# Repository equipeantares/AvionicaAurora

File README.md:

# Icaro-I (Aviônica Aurora V1.0)

## Introdução 

### Motivação

A equipe Antares de espaçomodelismo da Unicamp tem como um de seus projetos desenvolvidos o foguete Aurora. Trata-se de um foguete de propulsão sólida com apogeu esperado de 1km. Como parte dos requisitos necessários para ter sucesso na missão, o foguete precisa de um sistema de aviônica que será responsável por coletar dados e tomar decisões previamente programadas durante o voo. 

### Objetivo

Sendo assim, o objetivo deste projeto é desenvolver um sistema de aviônica capaz de detectar o apogeu programado e acionar o sistema de recuperação. Deve também ser capaz de transmitir os dados de voo ao solo em tempo real e coletar informações sobre a posição do foguete, possibilitando sua localização após aterrisagem. Além disso, deve ser dimensionada para caber na estrutura interna do foguete.

### Soluções comerciais

Pelo fato de o sistema precisar ser personalizado, se ajustando ao sistema presente no foguete e aos demais requisitos específicos do projeto, não existem alternativas comerciais que cumpram integralmente o objetivo.

## Especificação
    - Microcontrolador: o dispositivo deverá ser capaz de fazer processamentos lógicos, sendo assim necessário um microcontrolador. Por motivos de acessibilidade e familiaridade, será utilizada a plataforma Arduino no MCU ESP-8266 12F.

    - Comunicação e dados: com o objetivo de enviar dados de telemetria do foguete, o dispositivo deverá ter um sistema transceptor, que será implementado por um módulo LoRA E32-915T20D. Além disso, contará com uma interface para cartão MicroSD, possibilitando que os dados brutos sejam armazenados para uma análise mais precisa posterior.

    - Interface: como interface, o dispositivo contará com conectores para alimentação externa, além de pinos seletores, que selecionam, principalmente, se o sistema é o principal ou uma redundância e se o acionamento será interno ou externo (para testes).

    - Ignição: a aviônica precisa implementar um sistema de ignição que será o responsável pela liberação da recuperação.

    - Alimentação: o sistema tem interface de alimentação externa.

    - Redundância: o dispositivo implementa solução para um sistema com redundância nos subsistemas críticos, provendo maior segurança.

    - Localização: a fim de garantir que seja possível localizar o foguete após o pouso, o sistema deve ser capaz de transmitir a posição em tempo real por meio de um sistema GPS e de emitir um aviso sonoro por meio de um buzzer.

    - Detecção de apogeu: para ser capaz de detectar o momento do apogeu, a aviônica deve implementar um altímetro.

## Pinagem

### Pinout conector Screw bateria 18650

Pino | Sinal
-----|------
1  | VBat
2  | GND

### Pinout conector Screw do Acionamento

Pino | Sinal
-----|------
  1  | NiCr_ISO
  2  | GND_ISO

### Pinout conector Screw da Redundancia

Pino | Sinal
-----|------
  1  | Redundancy_IN
  2  | Redundancy_OUT

### Pinout conector Seleção Redundância

Pino | Sinal
-----|------
  1  | Redundancy_OUT
  2  | IGN
  3  | Main_IGN

### Pinout conector Transistor PNP acionamento (interno)

Pino | Sinal
-----|------
  1  | Emissor
  2  | Coletor

### Pinout conector Optoacoplador acionamento (externo)

Pino | Sinal
-----|------
  1  | Coletor
  2  | Emissor

## Testes

    A fim de garantir que o sistema seja seguro e que tudo funcione como esperado, é necessário realizar testes controlados de cada parte do sistema, tentando antecipar possíveis falhas que possam ocorrer. 
    Como o sistema de ignição não pode ter acionamento indesejado, devem ocorrer testes em ambientes adversos, como, por exemplo, com componentes desconectados, e o resultado esperado é que o sistema não ative em nenhuma dessas situações.
    Além disso, todos os sensores presentes devem ser validados.

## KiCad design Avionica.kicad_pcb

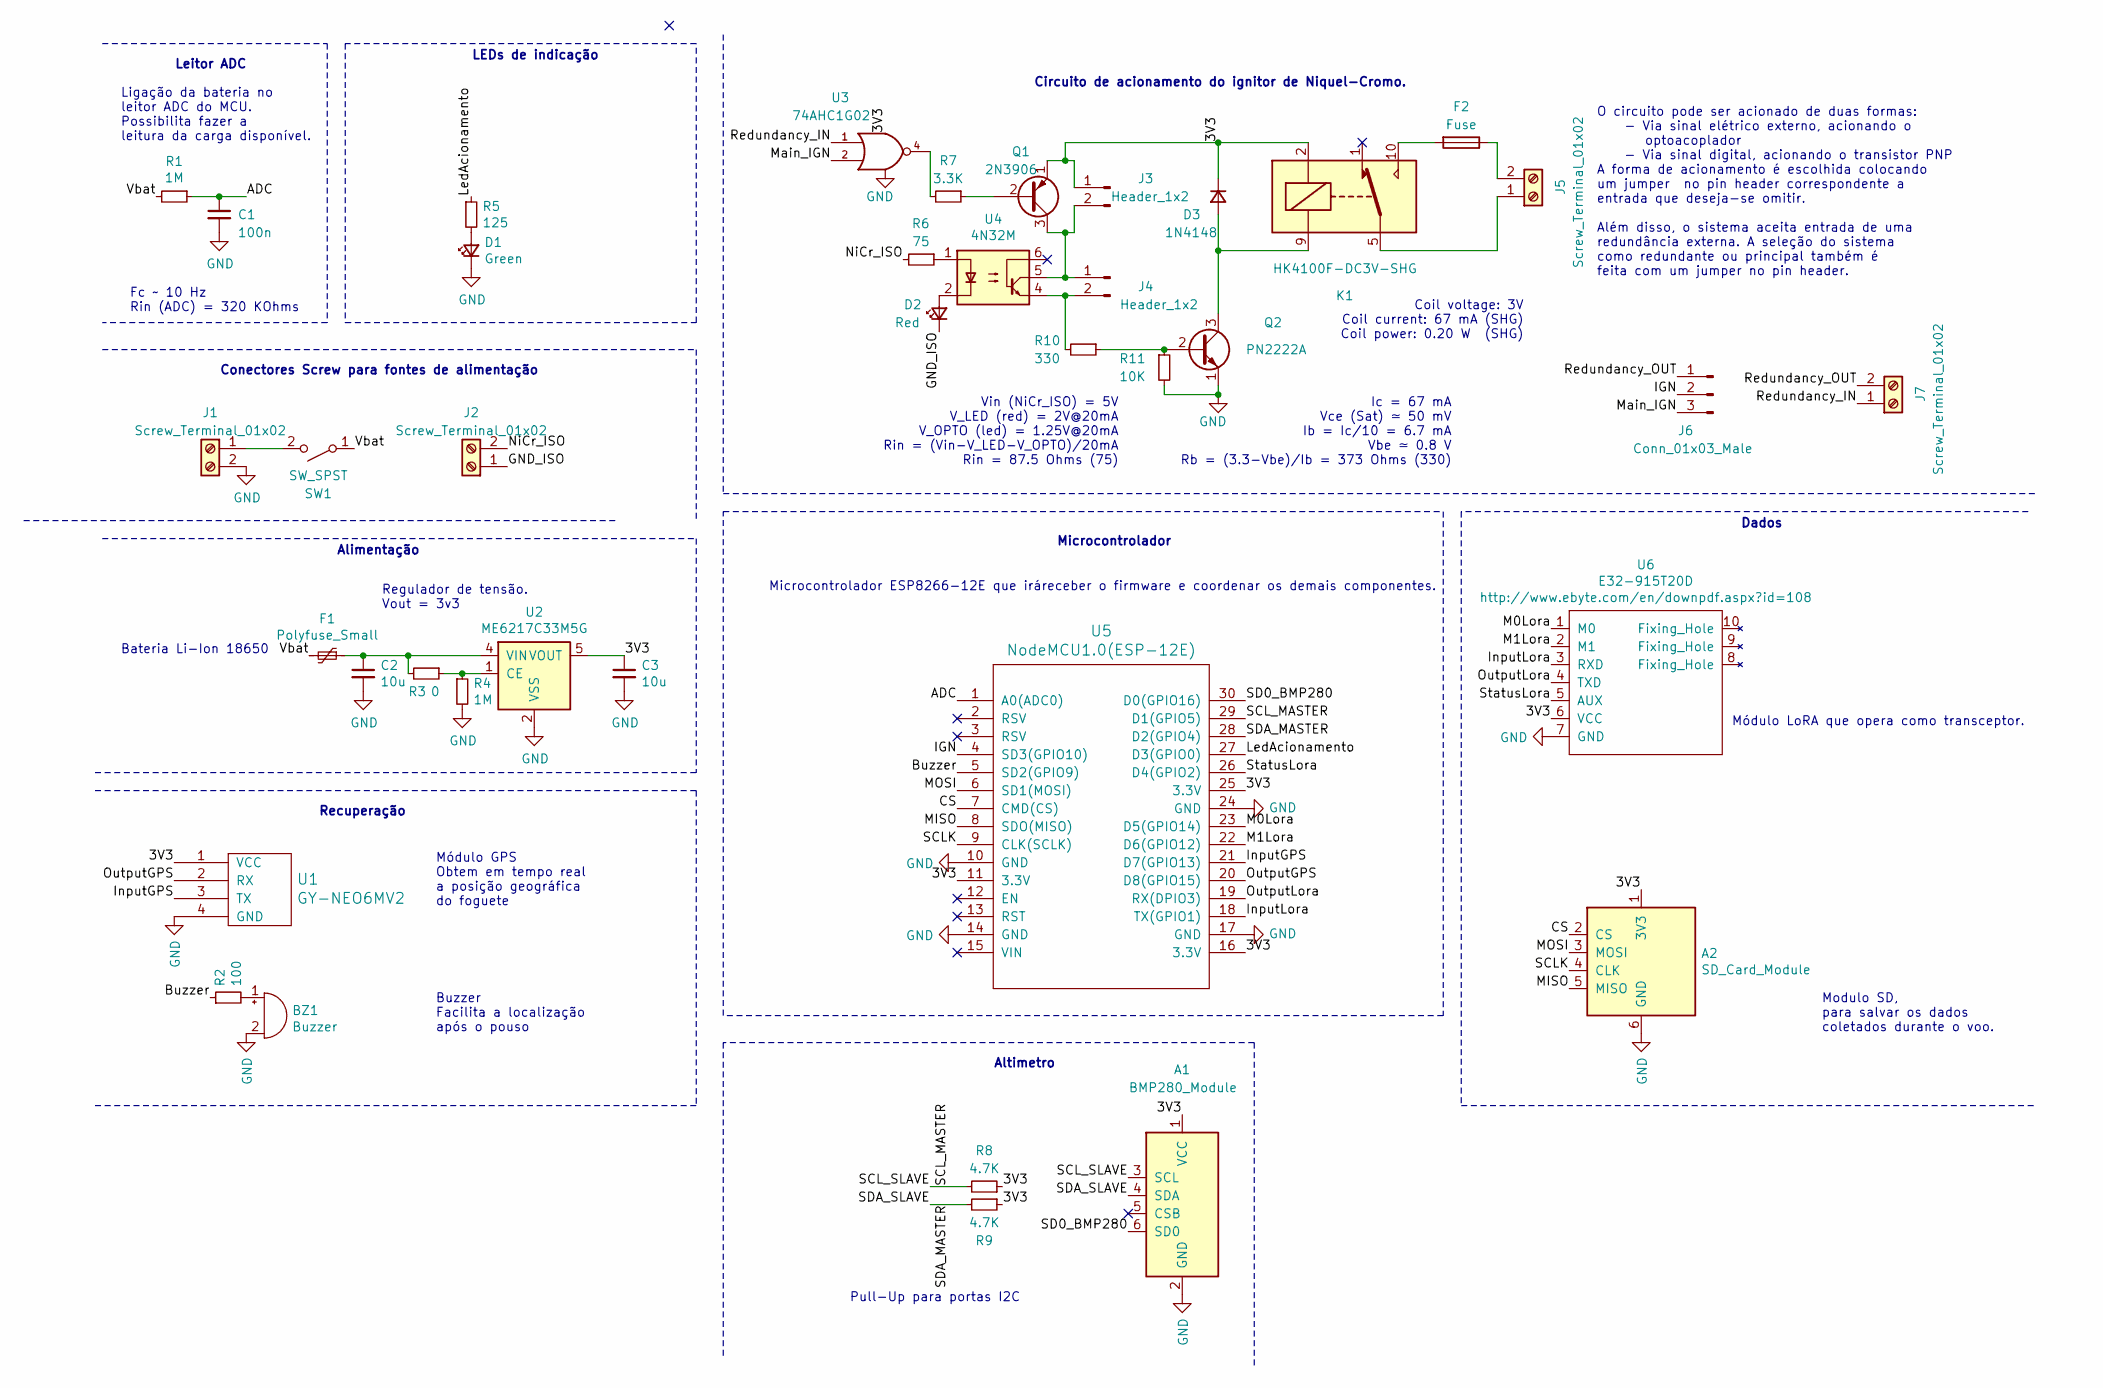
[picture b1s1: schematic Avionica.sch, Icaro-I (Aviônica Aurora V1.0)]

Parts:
A1: BMP280_Module
A2: SD_Card_Module
BZ1: Buzzer; Buzzer_12x9.5RM7.6
C1: 100n; C_0805_2012Metric
C2, C3: 10u; C_0805_2012Metric
D1: Green; LED_D3.0mm
D2: Red; LED_D3.0mm
D3: 1N4148; D_SOD-123
F1: Polyfuse_Small; Fuse_1206_3216Metric_Castellated
F2: Fuse; Fuseholder_Cylinder-5x20mm_Stelvio-Kontek_PTF78_Horizontal_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
J1, J2, J5, J7: Screw_Terminal_01x02; TerminalBlock_Phoenix_MKDS-1,5-2_1x02_P5.00mm_Horizontal
J3, J4: Header_1x2; Molex_KK-254_AE-6410-02A_1x02_P2.54mm_Vertical
J6: Conn_01x03_Male; Molex_KK-254_AE-6410-03A_1x03_P2.54mm_Vertical
K1: HK4100F-DC3V-SHG; Relay_SPDT_Omron_G5V-1
Q1: 2N3906; TO-92_Inline
Q2: PN2222A; TO-92_Inline
R1, R4: 1M; R_0805_2012Metric
R2: 100; R_0805_2012Metric
R3: 0; R_0805_2012Metric
R5: 125; R_0805_2012Metric
R6: 75; R_0805_2012Metric
R7: 3.3K; R_0805_2012Metric
R8, R9: 4.7K; R_0805_2012Metric
R10: 330; R_0805_2012Metric
R11: 10K; R_0805_2012Metric
SW1: SW_SPST; Screw_Switch
U1: GY-NEO6MV2
U2: ME6217C33M5G; SOT-23-5
U3: 74AHC1G02; SOT-23-5
U4: 4N32M; DIP-6_W7.62mm
U5: NodeMCU1.0(ESP-12E); ESP12F-Devkit-V3
U6: E32-915T20D; E32-xxxT20D

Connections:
/ADC: C1.1, R1.1, U5.1 (A0(ADC0))
/Buzzer: R2.1, U5.5 (SD2(GPIO9))
/CS: A2.2 (CS), U5.7 (CMD(CS))
/GND_ISO: D2.1 (K), J2.1
/IGN: J6.2, U5.4 (SD3(GPIO10))
/InputGPS: U1.3 (TX), U5.21 (D7(GPIO13))
/InputLora: U5.18 (TX(GPIO1)), U6.3 (RXD)
/LedAcionamento: R5.1, U5.27 (D3(GPIO0))
/M0Lora: U5.23 (D5(GPIO14)), U6.1 (M0)
/M1Lora: U5.22 (D6(GPIO12)), U6.2 (M1)
/MISO: A2.5 (MISO), U5.8 (SDO(MISO))
/MOSI: A2.3 (MOSI), U5.6 (SD1(MOSI))
/Main_IGN: J6.3, U3.2
/NiCr_ISO: J2.2, R6.2
/OutputGPS: U1.2 (RX), U5.20 (D8(GPIO15))
/OutputLora: U5.19 (RX(DPIO3)), U6.4 (TXD)
/Redundancy_IN: J7.1, U3.1
/Redundancy_OUT: J6.1, J7.2
/SCLK: A2.4 (CLK), U5.9 (CLK(SCLK))
/SCL_MASTER: A1.3 (SCL), R8.2, U5.29 (D1(GPIO5))
/SD0_BMP280: A1.6 (SD0), U5.30 (D0(GPIO16))
/SDA_MASTER: A1.4 (SDA), R9.2, U5.28 (D2(GPIO4))
/StatusLora: U5.26 (D4(GPIO2)), U6.5 (AUX)
/Vbat: F1.2, R1.2, SW1.1 (A)
GND: A1.2 (GND), A2.6 (GND), BZ1.2 (+), C1.2, C2.2, C3.2, D1.1 (K), J1.2, Q2.1 (E), R4.2, R11.2, U1.4 (GND), U2.2 (VSS), U3.3 (GND), U5.10 (GND), U5.14 (GND), U5.17 (GND), U5.24 (GND), U6.7 (GND)
unnamed: BZ1.1 (-), R2.2
unnamed: C2.1, F1.1, R3.2, U2.4 (VIN)
unnamed: D1.2 (A), R5.2
unnamed: D2.2 (A), U4.2
unnamed: D3.2 (A), K1.9, Q2.3 (C)
unnamed: F2.1, J5.2
unnamed: F2.2, K1.10
unnamed: J1.1, SW1.2 (B)
unnamed: J3.2, J4.1, Q1.3 (C), U4.5
unnamed: J4.2, R10.2, U4.4
unnamed: J5.1, K1.5, K1.6
unnamed: Q1.2 (B), R7.1
unnamed: Q2.2 (B), R10.1, R11.1
unnamed: R3.1, R4.1, U2.1 (CE)
unnamed: R6.1, U4.1
unnamed: R7.2, U3.4
VCC: A1.1 (VCC), A2.1 (3V3), C3.1, D3.1 (K), J3.1, K1.2, Q1.1 (E), R8.1, R9.1, U1.1 (VCC), U2.5 (VOUT), U3.5 (VCC), U5.11 (3.3V), U5.16 (3.3V), U5.25 (3.3V), U6.6 (VCC)

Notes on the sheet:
Coil voltage: 3V Coil current: 67 mA (SHG) Coil power: 0.20 W (SHG)
Fc ~~ 10 Hz Rin (ADC) = 320 KOhms
Regulador de tensão. Vout = 3v3
Conectores Screw para fontes de alimentação
LEDs de indicação
Ligação da bateria no leitor ADC do MCU. Possibilita fazer a leitura da carga disponível.
Módulo LoRA que opera como transceptor.
Microcontrolador ESP8266-12E que iráreceber o firmware e coordenar os demais componentes.
O circuito pode ser acionado de duas formas: - Via sinal elétrico externo, acionando o optoacoplador - Via sinal digital, acionando o transistor PNP A forma de acionamento é escolhida colocando um jumper no pin header correspondente a entrada que deseja-se omitir. Além disso, o sistema aceita entra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
Microcontrolador
Dados
Bateria Li-Ion 18650
Alimentação
Leitor ADC
Circuito de acionamento do ignitor de Niquel-Cromo.
Ic = 67 mA Vce (Sat) ≃ 50 mV Ib = Ic/10 = 6.7 mA Vbe ≃ 0.8 V Rb = (3.3-Vbe)/Ib = 373 Ohms (330)
Vin (NiCr_ISO) = 5V V_LED (red) = 2V@20mA V_OPTO (led) = 1.25V@20mA Rin = (Vin-V_LED-V_OPTO)/20mA Rin = 87.5 Ohms (75)
Recuperação
Altimetro
Pull-Up para portas I2C
Modulo SD, para salvar os dados coletados durante o voo.
Módulo GPS Obtem em tempo real a posição geográfica do foguete
Buzzer Facilita a localização após o pouso

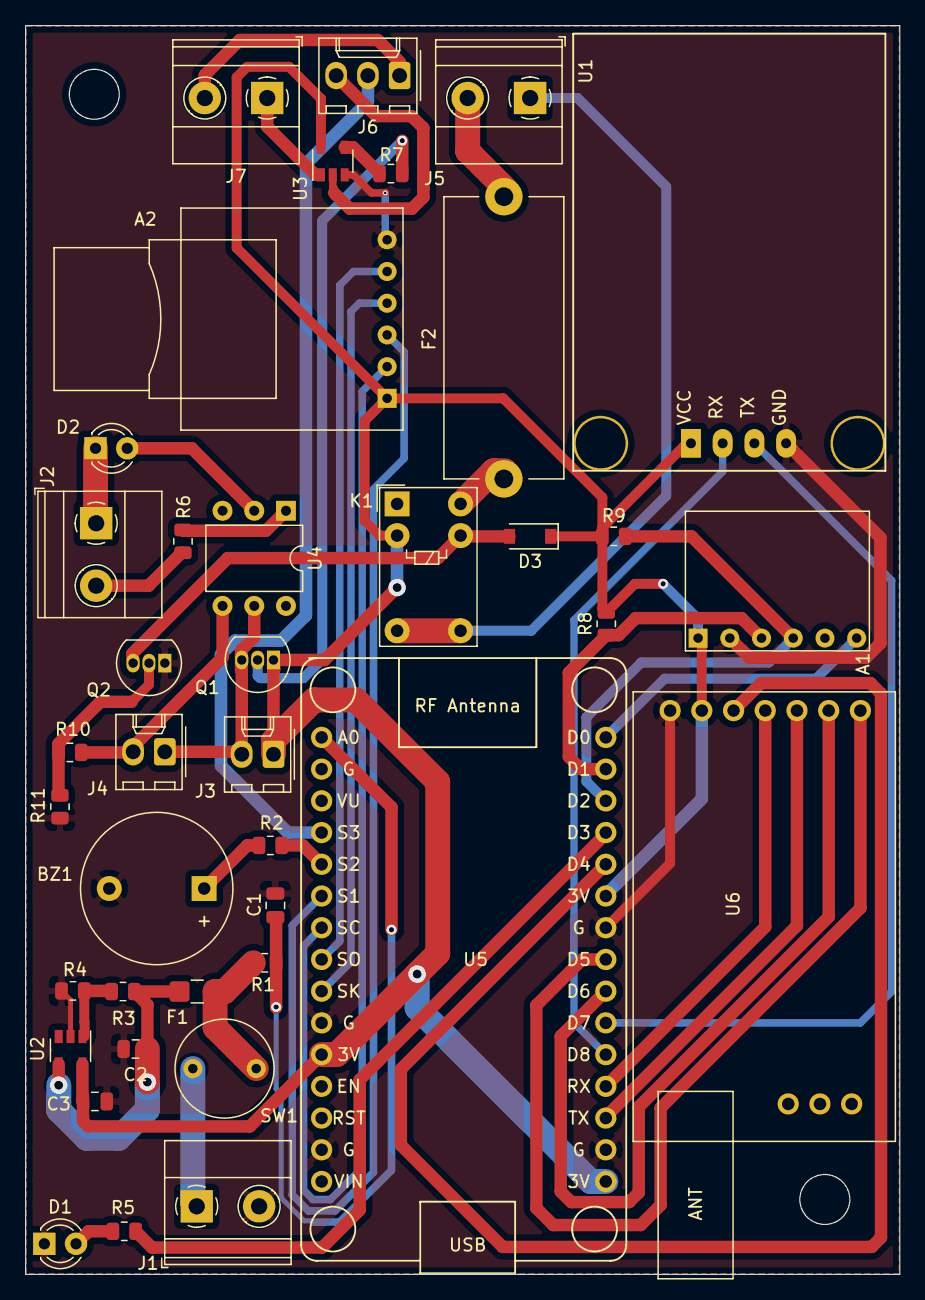
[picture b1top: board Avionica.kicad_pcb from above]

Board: 2 copper layers, 70.0 x 100.0 mm, 39 parts (0 on the bottom side), 42 nets.

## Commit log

2022-04-21 Primeira versão do projeto de aviônica Ícaro-I
